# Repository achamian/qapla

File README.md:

# Qapla

## Qapla 60 key keyboard

Qapla is a 60 key keyboard with Choc or MX switches inspired by Lilly58 and Sofle. Columns have splay and stagger based on my cardboard mocks.

For designing the layout it uses

* [Ergogen](https://github.com/ergogen/ergogen) to define layout, generate PCB and case.
* [Ceoloide Footprints](https://github.com/achamian/ergogen-footprints/tree/diode_via_connections) to add footprints (It is a fork which adds via pads for diodes).
* Routing is done in KiCad.

## Components and Jumpers

### MCU

* Solder jumpers on the front if controller is mounted on top of the pcb facing it
* Solder jumpers on the back if controller is mounted on top of the pcb facing away from it
* Solder jumpers on the back if controller is mounted under the pcb facing it
* Solder jumpers on the front if controller is mounted under the pcb facing away from it

## Display

Qapla supports Nice!View reversible footprint. To use I2C OLED display instead of Nice!View connect display to inner four pins on the left half and outer four pins on the right half. Bridge jumpers on the opposite side of the display.

### JST Battery Connector

Bridge jumpers on the opposite side of the connector. Note the polarity when connecting the battery.

## Bill of Materials

| Quantity | Component | Notes |
|----------|-----------|-------|
| 2 | PCB | Left and right halves |
| 2 | Pro Micro compatible MCU | e.g., Nice!Nano for wireless |
| 60 | Choc or MX switches | Depending on preference |
| 60 | Diodes (1N4148 or similar) | SOD-123 |
| 2 | Reset switches | |
| 2 | JS102011SAQN SMT slide switch | |
| 2 | Nice!View or OLED displays | Optional |
| 56 | Keycaps 1u | Compatible with chosen switches |
| 4 | Keycaps 1.5u | Compatible with chosen switches |
| 10 | M2 3mm screws | For case assembly |
| 10 | M2 heat inserts OD: 3.2mm, Length: 3mm | For case assembly [AliExpress](https://vi.aliexpress.com/item/1005003582355741.html)|
| 2 | Blue SMD standard LED | 0805(2012 metric) - Optional - Battery Indicator|
| 2 | 220 Ohm SMD resistors | 0805(2012 metric) - Optional - Battery Indicator|

## Links

* [Introduction to Ergogen](https://flatfootfox.com/ergogen-introduction/)
* [ZMK Keymap Editor](https://nickcoutsos.github.io/keymap-editor/)
* [Keymap Layout Tool](https://nickcoutsos.github.io/keymap-layout-tools/)

## Firmware

* ZMK Firmware is in a [sister repository](https://github.com/achamian/qapla-zmk-config)

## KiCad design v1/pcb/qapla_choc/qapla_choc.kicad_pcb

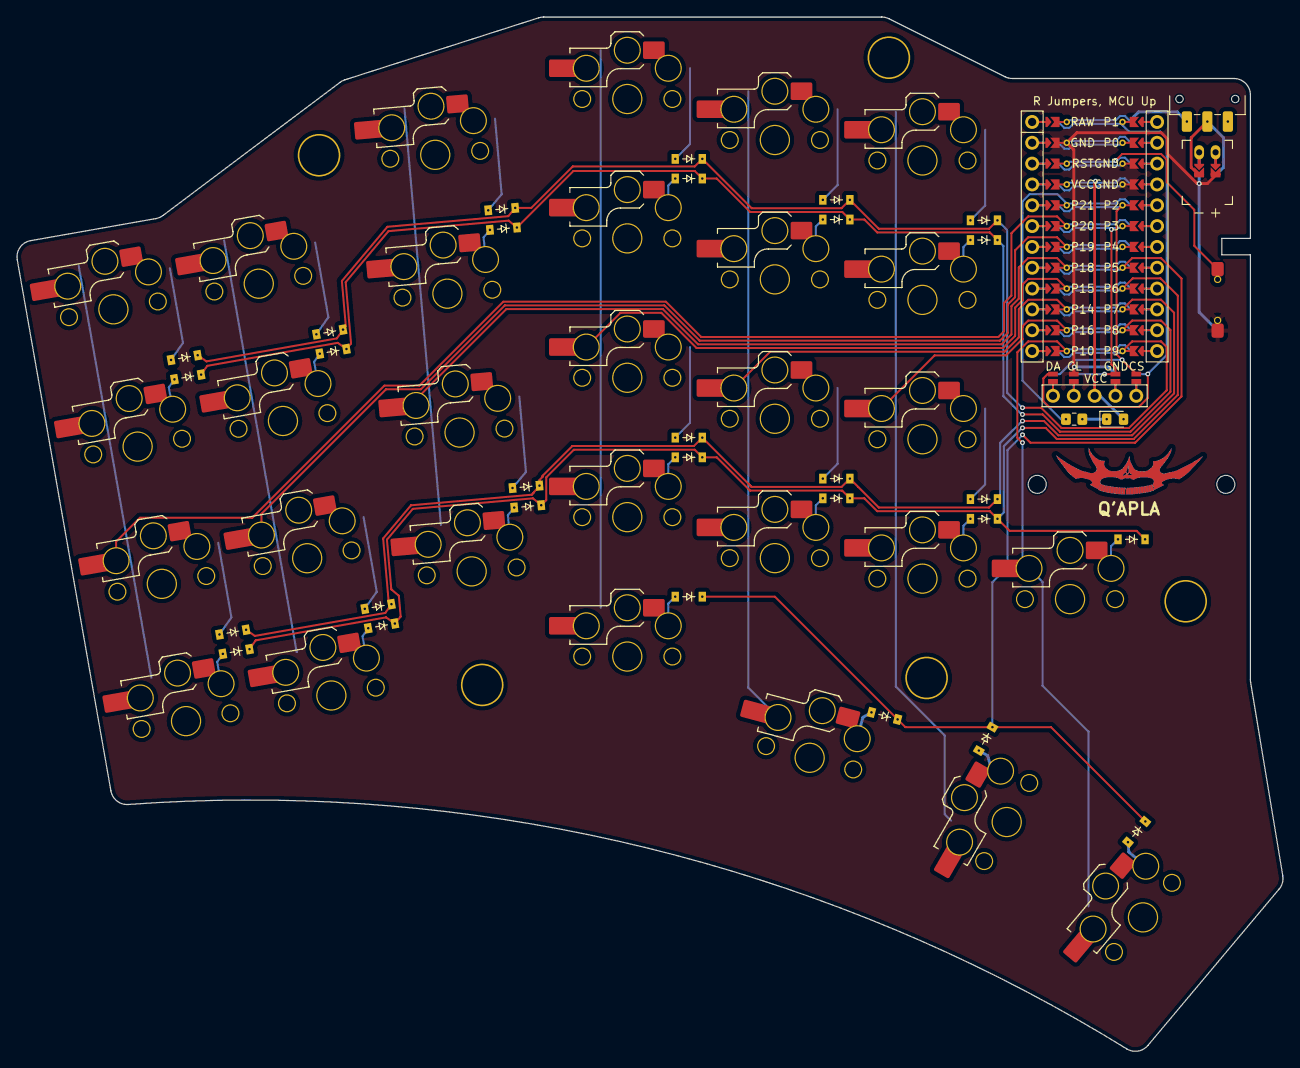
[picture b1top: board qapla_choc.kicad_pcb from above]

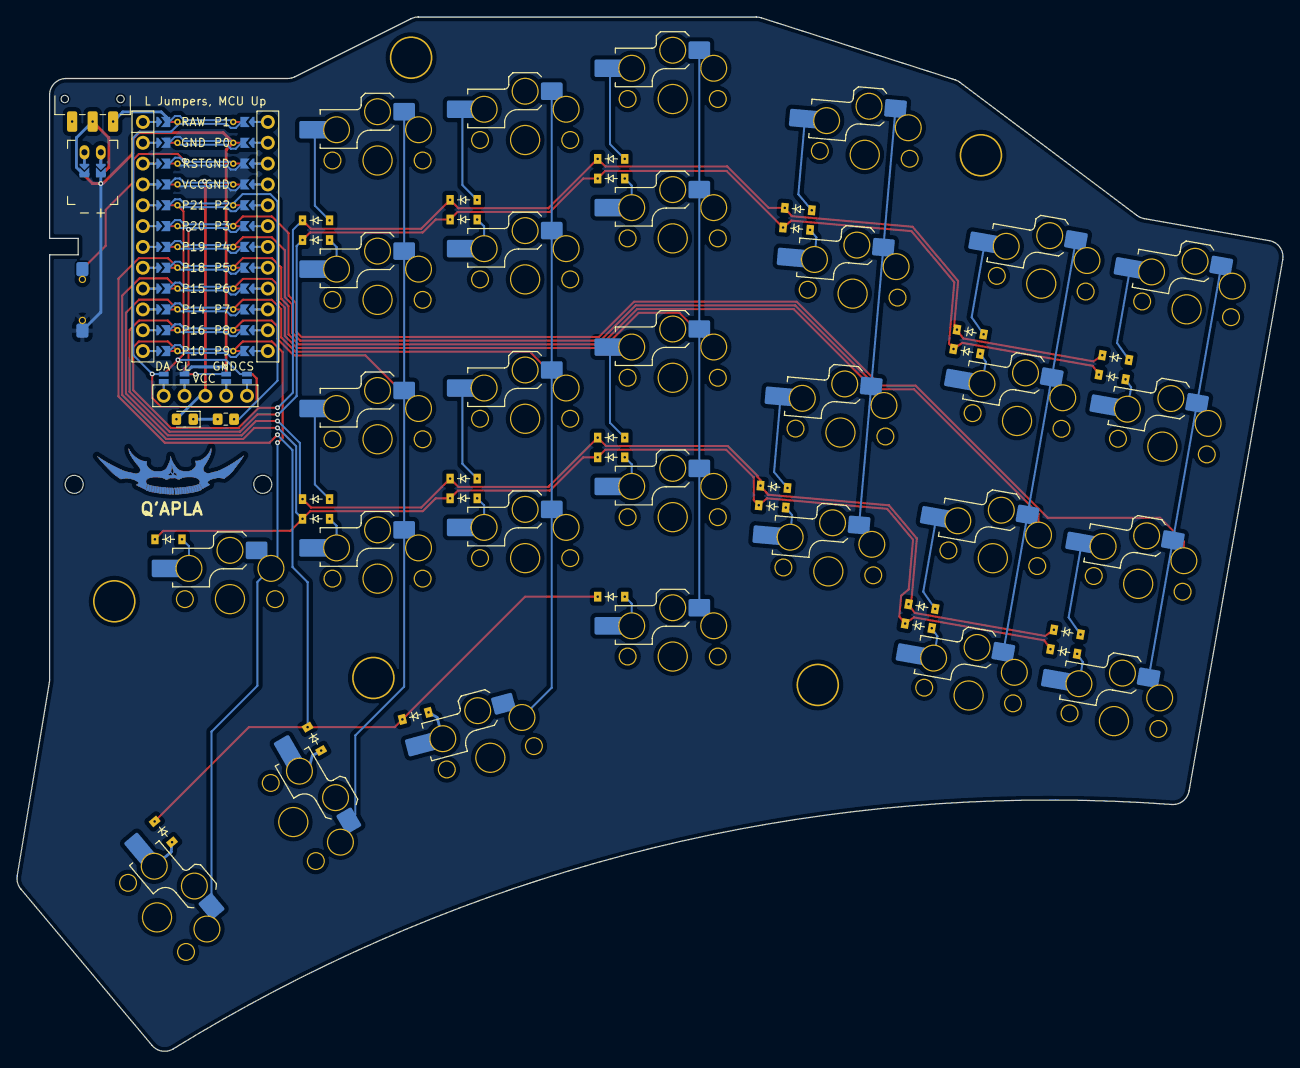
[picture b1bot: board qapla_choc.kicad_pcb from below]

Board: 2 copper layers, 154.4 x 126.1 mm, 72 parts (58 on the bottom side), 57 nets.

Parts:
D1, D2, D3, D4, D5, D6, D7, D8, D9, D10, D11, D12, D13, D14, D15, D16, D17, D18, D19, D20, D21, D22, D23, D24, D25, D26, D27, D28, D29: diode_tht_sod123
DISP1: display_nice_view
H1, H2, H3, H4, H5: mounting_hole_plated
JST1: battery_connector_jst_ph_2
MCU1: mcu_nice_nano
MH1, MH2: mounting_hole_npth
S1, S2, S3, S4, S5, S6, S7, S8, S9, S10, S11, S12, S13, S14, S15, S16, S17, S18, S19, S20, S21, S22, S23, S24, S25, S26, S27, S28, S29: switch_choc_v1_v2
_1: reset_switch
_2: switch_JS102011SAQN
_3: D_0805_2012Metric_Pad1.15x1.40mm_HandSolder
_3#2: R_0805_2012Metric_Pad1.20x1.40mm_HandSolder

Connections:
BAT_P: JST1.1, _2.2
DISP1_1: DISP1.1, DISP1.10, DISP1.23
DISP1_2: DISP1.2, DISP1.11, DISP1.22
DISP1_4: DISP1.4, DISP1.12, DISP1.21
DISP1_5: DISP1.5, DISP1.13, DISP1.20
GND: DISP1.15, DISP1.25, JST1.2, MCU1.103, MCU1.104, MCU1.123, _1.1, _1.3
JST1_1: JST1.11, JST1.21, JST1.31
JST1_2: JST1.12, JST1.22, JST1.32
P1: DISP1.14, DISP1.24, MCU1.101
P2: DISP1.17, DISP1.27, MCU1.105
P3: DISP1.16, DISP1.26, MCU1.106
P5: D19.1, D27.1, D28.1, D29.1, MCU1.108
P6: D13.1, D15.1, D17.1, D20.1, D22.1, D24.1, D26.1, MCU1.109
P7: D1.1, D3.1, D5.1, D7.1, D9.1, D11.1, MCU1.110
P8: D14.1, D16.1, D18.1, D21.1, D23.1, D25.1, MCU1.111
P9: D2.1, D4.1, D6.1, D8.1, D10.1, D12.1, MCU1.112
P10: MCU1.113, S26.1, S29.1
P14: MCU1.115, S18.1, S19.1, S20.1, S21.1, S27.1
P15: MCU1.116, S13.1, S14.1, S15.1, S16.1, S17.1
P16: MCU1.114, S22.1, S23.1, S24.1, S25.1, S28.1
P18: MCU1.117, S9.1, S10.1, S11.1, S12.1
P19: MCU1.118, S5.1, S6.1, S7.1, S8.1
P20: MCU1.119, S1.1, S2.1, S3.1, S4.1
P21: MCU1.120, _3#2.3
RAW: MCU1.124, _2.3
RST: MCU1.122, _1.2, _1.4
VCC: DISP1.3, MCU1.121, _3.2
_3_1: _3.1, _3#2.4
alt_mod: D27.2, S27.2
index_bottom: D22.2, S18.2
index_home: D9.2, S19.2
index_num: D10.2, S21.2
index_top: D23.2, S20.2
inner_bottom: D24.2, S22.2
inner_far_bottom: D26.2, S26.2
inner_home: D11.2, S23.2
inner_mod: D28.2, S28.2
inner_num: D12.2, S25.2
inner_top: D25.2, S24.2
middle_bottom: D20.2, S14.2
middle_home: D7.2, S15.2
middle_mod: D19.2, S13.2
middle_num: D8.2, S17.2
middle_top: D21.2, S16.2
outer_bottom: D13.2, S1.2
outer_home: D1.2, S2.2
outer_mod: D29.2, S29.2
outer_num: D2.2, S4.2
outer_top: D14.2, S3.2
pinky_bottom: D15.2, S5.2
pinky_home: D3.2, S6.2
pinky_num: D4.2, S8.2
pinky_top: D16.2, S7.2
ring_bottom: D17.2, S9.2
ring_home: D5.2, S10.2
ring_num: D6.2, S12.2
ring_top: D18.2, S11.2

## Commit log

2024-08-22 Let there be light!
2024-08-22 Add basic key layout
2024-08-22 Define plate
2024-08-22 Plate with keycaps
2024-08-22 Adding space for MCU on the board
2024-08-22 Start building PCB
2024-08-22 Adding ceoloide footprint from a fork
2024-08-22 Modify README to include links and add LICENCE
2024-08-22 Creating a KiCad project
2024-08-23 Adding mx switch support
2024-08-23 Adding diodes and mcu
2024-08-23 Adding nets for keys, reset switch and display
2024-08-23 Adding JS102011SAQN switch
2024-08-26 Positioning reset switch, jst connector and power switch
2024-08-26 All components in place except mounting holes
2024-08-26 Adding mounting holes
2024-08-26 Adding holes for display plate
2024-08-27 Adding bottom plate
2024-08-27 Moving mount points to board instead of ergogen yaml parent
2024-08-27 Adjusting hole positions
2024-08-28 Starting work on bottom case
2024-08-28 Finalising Plate and PCB design for choc
2024-08-29 Adjusting distance between diodes to accomodate traces
2024-08-29 Adding bottom case
2024-08-29 Fixing hole size for heat inserts
2024-08-29 Moving files to choc directory
2024-08-29 Adding MX footprints and ergogen config
2024-08-29 Renaming kicad project
2024-08-29 Finalize MX case and PCB design
2024-08-30 Routing MX switches
2024-08-30 Adding GPIO param to resistor_led_0805_2012Metric footprint
2024-08-30 Finalizing Qapla MX PCB
2024-08-30 Adding OLED cover plate for MX case
2024-08-30 Finalize choc case and pcb design
2024-08-30 Changing battery LED net
2024-08-30 MX Keyboard has a batleth
2024-08-30 Choc keyboard routing done
2024-09-03 Merging choc and mx into one config
2024-09-03 Add missing components to the BOM
2024-09-03 Update BOM
2024-09-06 Porting over zmk spike configuration
2024-09-06 Adding github actions for building zmk configs
2024-09-06 Updating zmk-config path for github actions
2024-09-06 Provide build matrix and config path for github actions
2024-09-06 Remove submodule
2024-09-06 Moving zmk-config to a different repo
2024-09-10 Adding reference links to README
